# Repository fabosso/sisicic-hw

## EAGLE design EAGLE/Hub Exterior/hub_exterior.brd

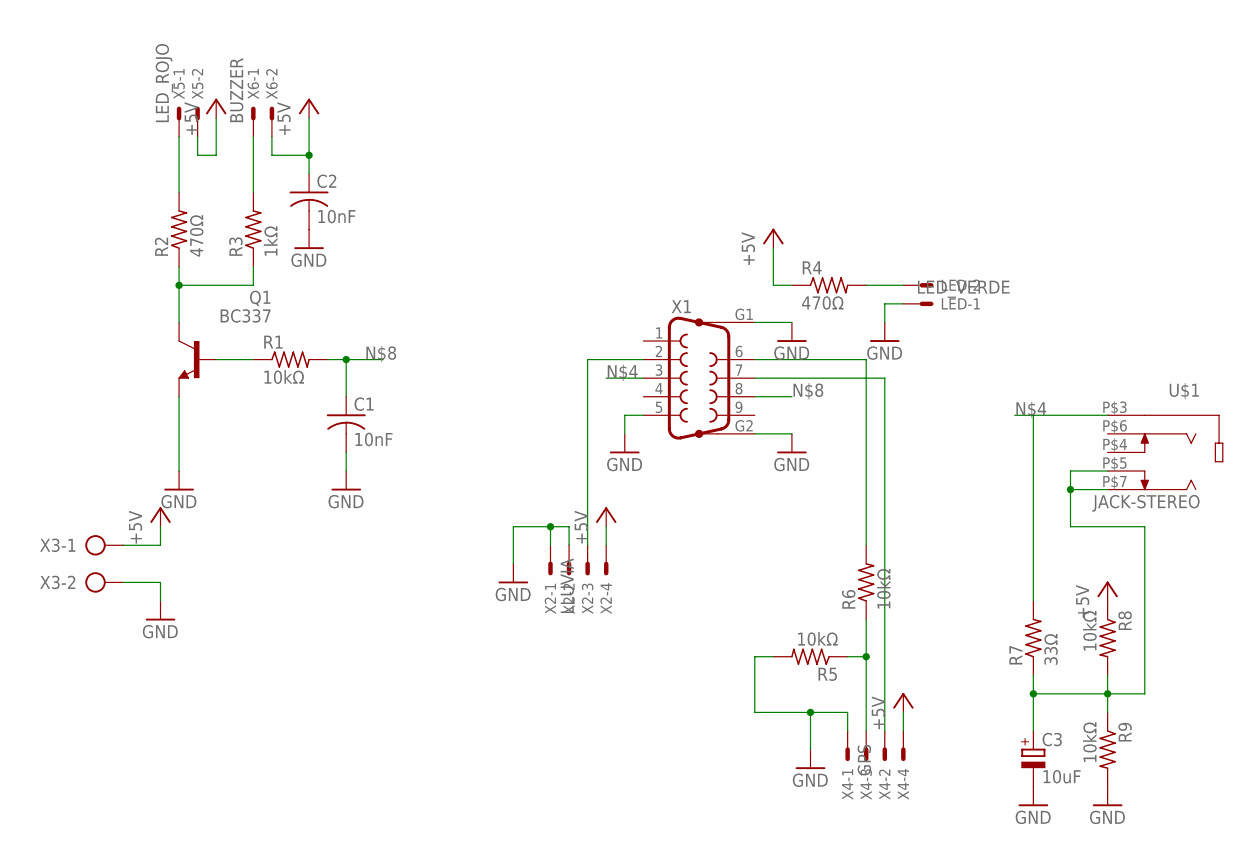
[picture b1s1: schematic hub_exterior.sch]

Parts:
C1, C2: 10nF; C050-025X075
C3: 10uF; E2,5-5
LED: LED_VERDE; 22-23-2021
Q1: BC337; TO92
R1, R5, R8, R9: 10kΩ; 0207/7
R2, R4: 470Ω; 0207/7
R3: 1kΩ; 0207/7
R6: 10kΩ; 0207/15
R7: 33Ω; 0207/7
U$1: JACK-STEREO; SPC21348
X1: F09HP
X2: LLUVIA; 22-23-2041
X3: AK500/2
X4: GPS; 22-23-2041
X5: LED_ROJO; 22-23-2021
X6: BUZZER; 22-23-2021

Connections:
+5V: C2.1, R4.1, R8.1, X2.4, X3.1, X4.4, X5.2, X6.2
GND: C1.2, C2.2, C3.-, LED.1, Q1.1 (E), R5.2, R9.2, X1.5, X1.G1, X1.G2, X2.1, X2.2, X3.2, X4.1
unnamed: Q1.2 (B), R1.1
unnamed: LED.2, R4.2
unnamed: Q1.3 (C), R2.1, R3.1
unnamed: R7.2, U$1.P$3 (1), X1.3
unnamed: R2.2, X5.1
unnamed: R3.2, X6.1
unnamed: X1.2, X2.3
unnamed: C1.1, R1.2, X1.8
unnamed: X1.7, X4.2
unnamed: R6.2, X1.6
unnamed: R5.1, R6.1, X4.3
unnamed: C3.+, R7.1, R8.2, R9.1, U$1.P$5 (4), U$1.P$7 (5)

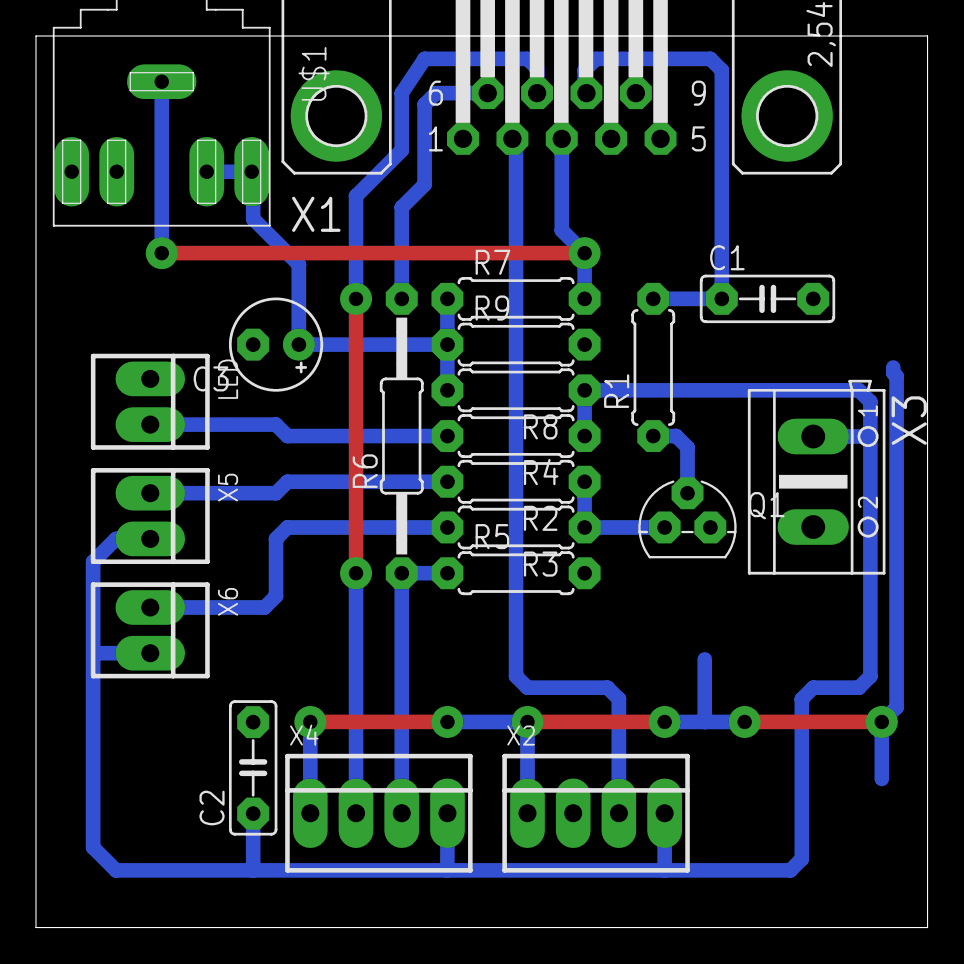
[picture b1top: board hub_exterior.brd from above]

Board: 2 copper layers, 49.5 x 49.5 mm, 21 parts (0 on the bottom side), 14 nets.

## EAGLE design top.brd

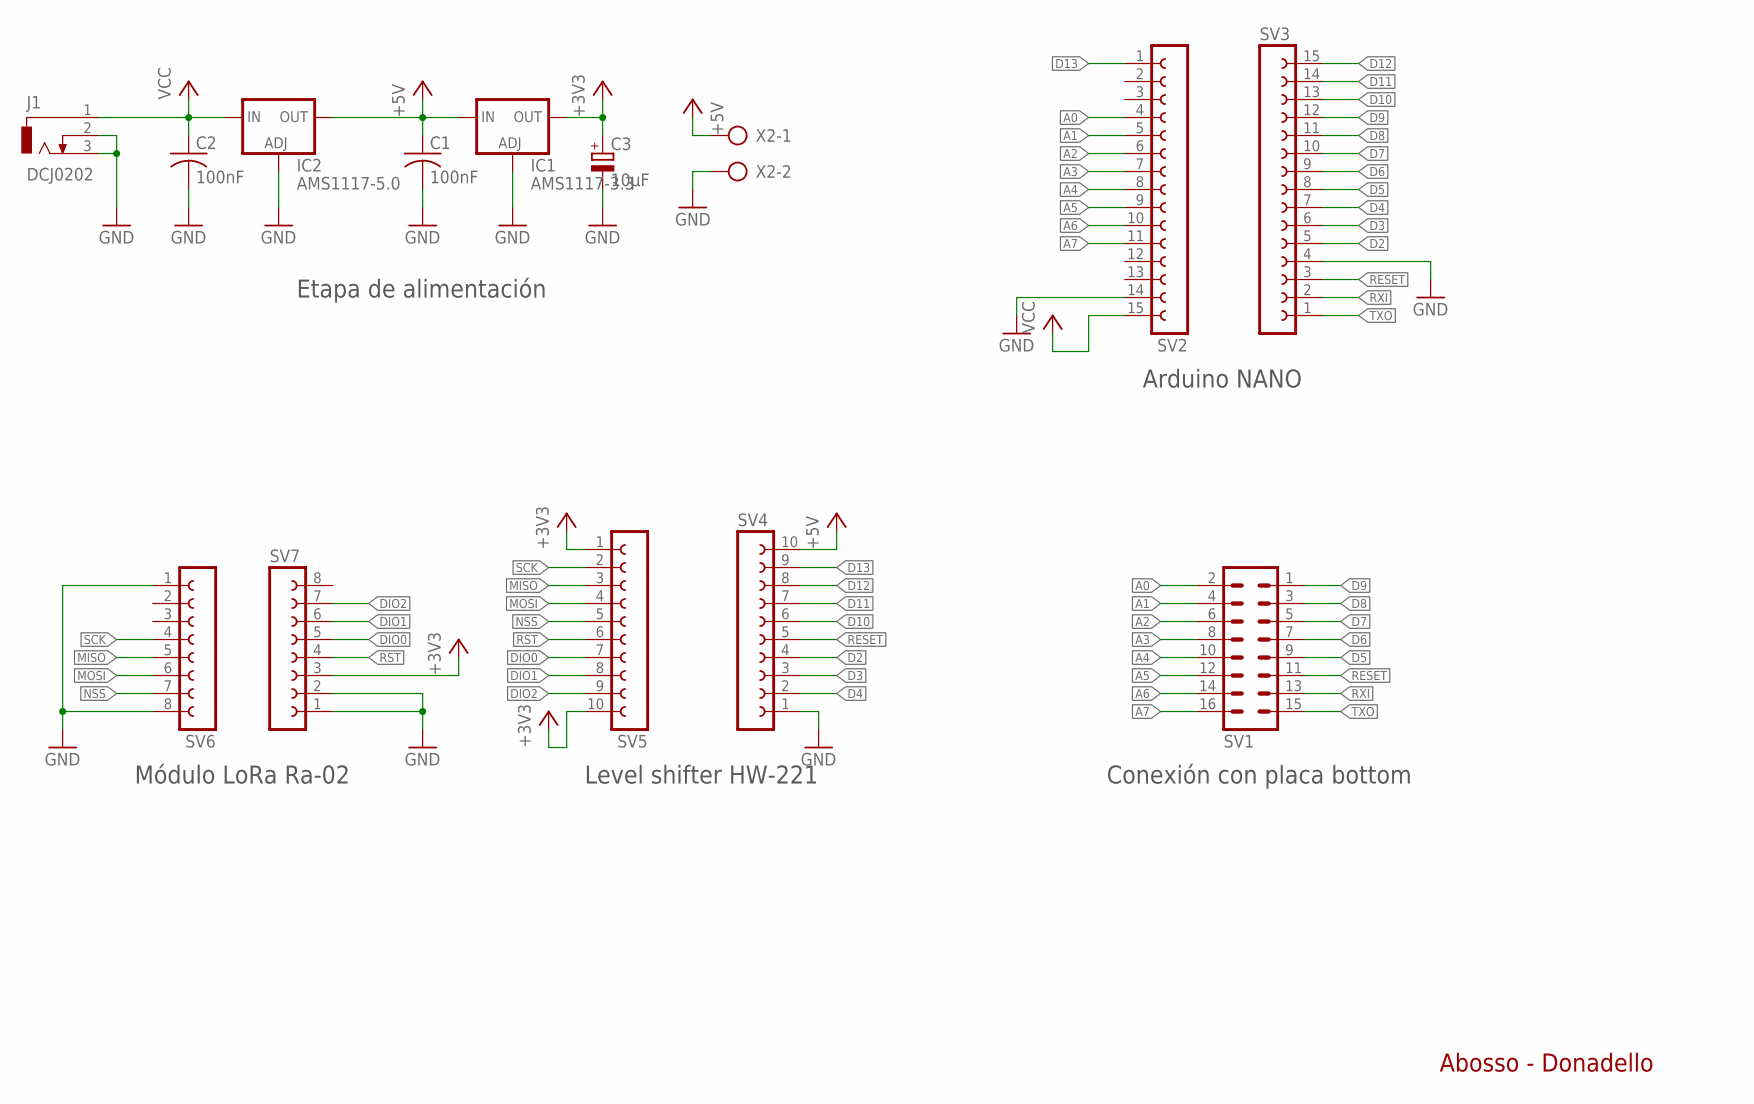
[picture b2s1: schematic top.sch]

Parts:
C1, C2: 100nF; C0805
C3: 10µF; PANASONIC_B
IC1: AMS1117-3.3; SOT223
IC2: AMS1117-5.0; SOT223
J1: DCJ0202
SV1: MA08-2
SV2, SV3: FE15-1; FE15
SV4, SV5: FE10-1; FE10
SV6, SV7: FE08-1; FE08
X2: AK500/2

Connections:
+3V3: C3.+, IC1.4 (OUT), SV5.1, SV5.10, SV7.3
+5V: C1.1, IC1.3 (IN), IC2.4 (OUT), SV4.10, X2.1
A0: SV1.2, SV2.4
A1: SV1.4, SV2.5
A2: SV1.6, SV2.6
A3: SV1.8, SV2.7
A4: SV1.10, SV2.8
A5: SV1.12, SV2.9
A6: SV1.14, SV2.10
A7: SV1.16, SV2.11
D2: SV3.5, SV4.4
D3: SV3.6, SV4.3
D4: SV3.7, SV4.2
D5: SV1.9, SV3.8
D6: SV1.7, SV3.9
D7: SV1.5, SV3.10
D8: SV1.3, SV3.11
D9: SV1.1, SV3.12
D10: SV3.13, SV4.6
D11: SV3.14, SV4.7
D12: SV3.15, SV4.8
D13: SV2.1, SV4.9
DIO0: SV5.7, SV7.5
DIO1: SV5.8, SV7.6
DIO2: SV5.9, SV7.7
GND: C1.2, C2.2, C3.-, IC1.1 (ADJ), IC2.1 (ADJ), J1.2, J1.3, SV2.14, SV3.4, SV4.1, SV6.1, SV6.8, SV7.1, SV7.2, X2.2
MISO: SV5.3, SV6.5
MOSI: SV5.4, SV6.6
NSS: SV5.5, SV6.7
RESET: SV1.11, SV3.3, SV4.5
RST: SV5.6, SV7.4
RXI: SV1.13, SV3.2
SCK: SV5.2, SV6.4
TXO: SV1.15, SV3.1
VCC: C2.1, IC2.3 (IN), J1.1, SV2.15

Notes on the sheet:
Módulo LoRa Ra-02
Level shifter HW-221
Etapa de alimentación
Conexión con placa bottom
Arduino NANO
Abosso - Donadello

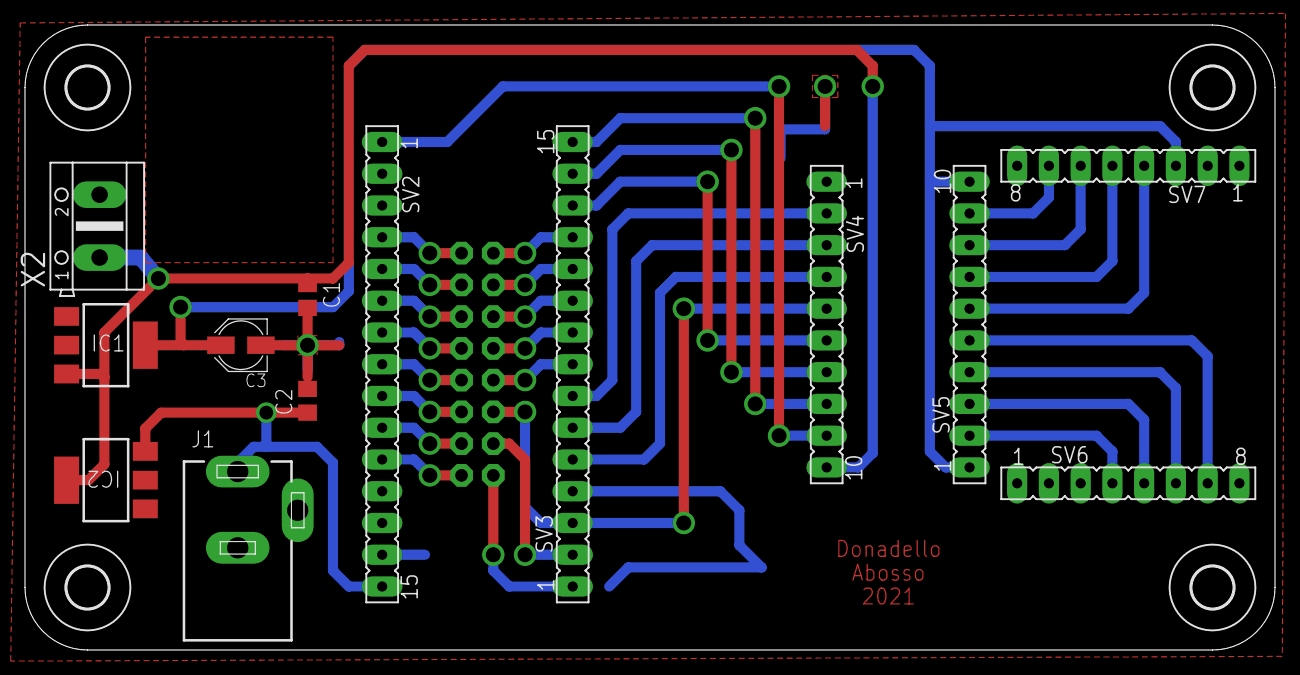
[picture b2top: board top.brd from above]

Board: 2 copper layers, 100.0 x 50.0 mm, 18 parts (1 on the bottom side), 35 nets.

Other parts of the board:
U$1, U$2, U$3, U$4: 3,3

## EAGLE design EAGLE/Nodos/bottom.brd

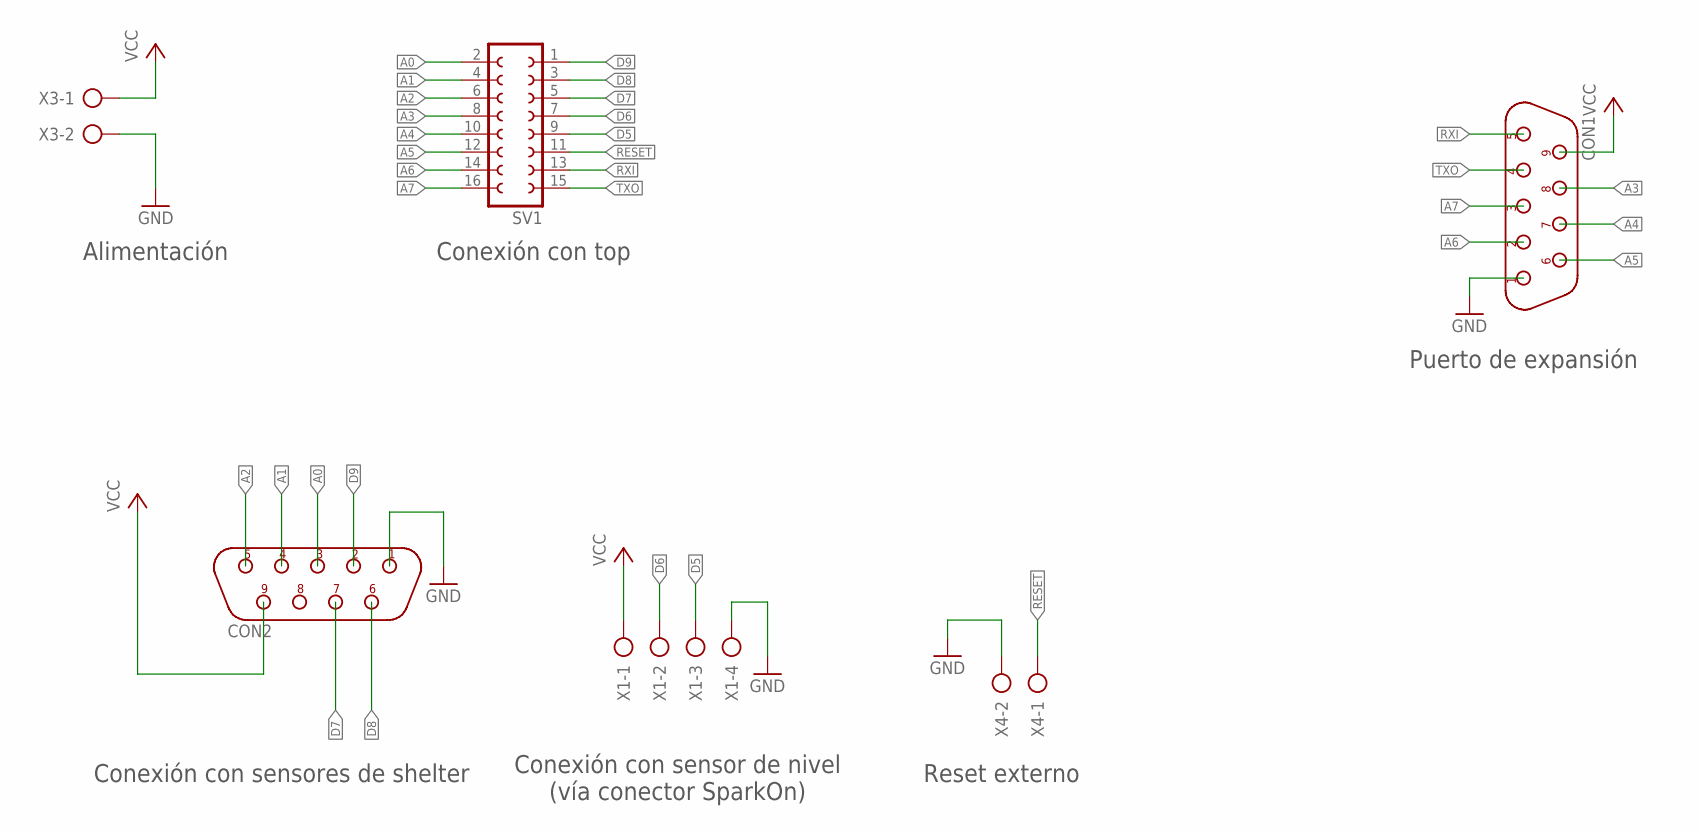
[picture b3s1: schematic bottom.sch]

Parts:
CON1, CON2: DB9M/90; D-09M/90
SV1: FE08-2
X1: AK500/4
X3, X4: AK500/2

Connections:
A0: CON2.3, SV1.2
A1: CON2.4, SV1.4
A2: CON2.5, SV1.6
A3: CON1.8, SV1.8
A4: CON1.7, SV1.10
A5: CON1.6, SV1.12
A6: CON1.2, SV1.14
A7: CON1.3, SV1.16
D5: SV1.9, X1.3
D6: SV1.7, X1.2
D7: CON2.7, SV1.5
D8: CON2.6, SV1.3
D9: CON2.2, SV1.1
GND: CON1.1, CON2.1, X1.4, X3.2, X4.2
RESET: SV1.11, X4.1
RXI: CON1.5, SV1.13
TXO: CON1.4, SV1.15
VCC: CON1.9, CON2.9, X1.1, X3.1

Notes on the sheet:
Puerto de expansión
Alimentación
Conexión con top
Conexión con sensores de shelter
Conexión con sensor de nivel (vía conector SparkOn)
Reset externo

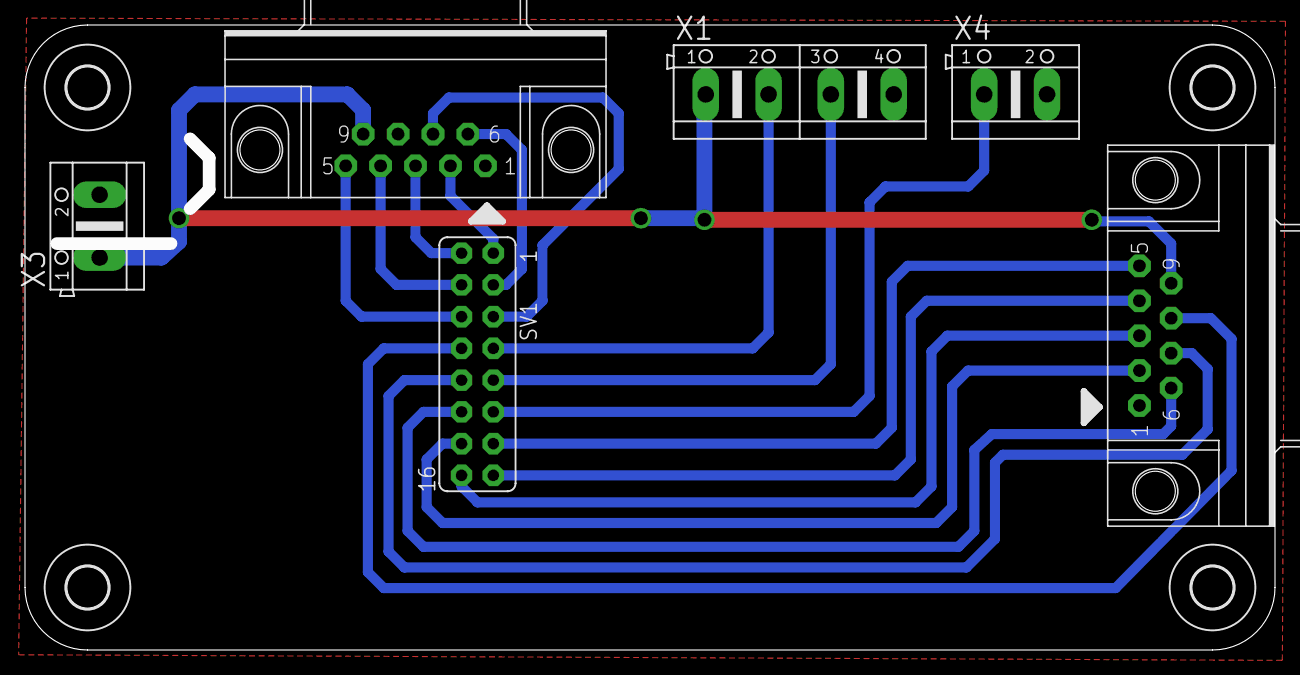
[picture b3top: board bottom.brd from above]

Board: 2 copper layers, 100.0 x 50.0 mm, 10 parts (0 on the bottom side), 18 nets.

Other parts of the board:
U$1, U$2, U$3, U$4: 3,3

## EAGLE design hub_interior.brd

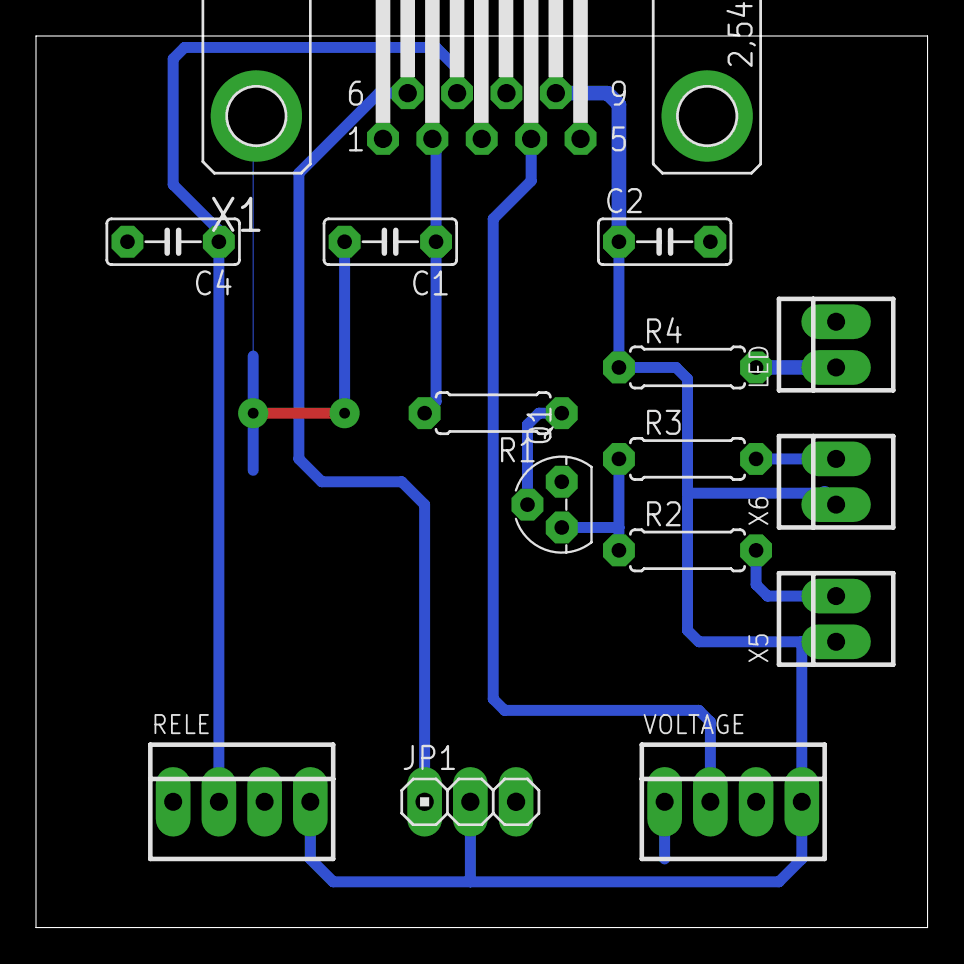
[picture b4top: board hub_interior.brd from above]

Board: 2 copper layers, 49.5 x 49.5 mm, 15 parts (0 on the bottom side), 11 nets.

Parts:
C1, C2: 10nF; C050-025X075
C4: C050-025X075
JP1: 1X03
LED: LED_VERDE; 22-23-2021
Q1: BC337; TO92
R1: 10kΩ; 0207/7
R2: 1kΩ; 0207/7
R3, R4: 470Ω; 0207/7
RELE: 22-23-2041
VOLTAGE: 22-23-2041
X1: F09HP
X5: BUZZER; 22-23-2021
X6: LED_ROJO; 22-23-2021

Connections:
+5V: C2.1, JP1.2, R4.1, RELE.4, VOLTAGE.4, X1.9, X5.1, X6.1
GND: C1.2, C2.2, C4.2, JP1.3, LED.2, Q1.1, RELE.1, RELE.3, VOLTAGE.1, VOLTAGE.3, X1.G1, X1.G2
unnamed: Q1.2, R1.1
unnamed: C1.1, R1.2, X1.2
unnamed: Q1.3, R2.1, R3.1
unnamed: C4.1, RELE.2, X1.7
unnamed: R2.2, X5.2
unnamed: R3.2, X6.2
unnamed: LED.1, R4.2
unnamed: VOLTAGE.2, X1.4
unnamed: JP1.1, X1.6

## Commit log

2021-03-30 Add files via upload
    Añadidos archivos .brd y .sch
2021-03-30 Add files via upload
    Añadidos .lbr de eagle
2022-07-27 add files hub interior
2022-07-27 add files hub exterior
2022-07-27 add libraries
2022-08-19 Relocations
2022-08-19 Relocation bis
2022-08-19 Update EAGLE files (hub exterior)
2022-08-19 KiCAD and FlatCAM upload files
2022-08-24 rediseño hub interior
2022-08-24 rediseño hub exterior
2022-08-24 añadir software utilizado
2022-08-24 añadida carpeta docs
2022-08-24 engrosado pads hub interior
2022-08-24 engrosado pads hub exterior
